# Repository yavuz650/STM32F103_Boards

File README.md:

# STM32F103 Boards
Rocket avionic boards, powered by the STM32F103C8T6 MCU.

This repository contains files and documentations of two avionic boards designed and developed for the Rocket Technologies Group of Istanbul Technical University in the year 2018. 

## Igniter Board
This board is designed to gather altitude data and control rocket's parachute deployment system. It was designed and programmed by Yavuz Selim Tozlu, assisted by Umit Yelken and L. Emre Top of Rocket Technologies Group.

## GPS Board
This board is designed to gather GPS data during flight, process it and send it to the ground station via the RF module attached to it. It was designed and programmed by Yavuz Selim Tozlu. 

Shout out goes to our [sponsor](http://www.megasistem.net) who was kind enough to manufacture the boards.

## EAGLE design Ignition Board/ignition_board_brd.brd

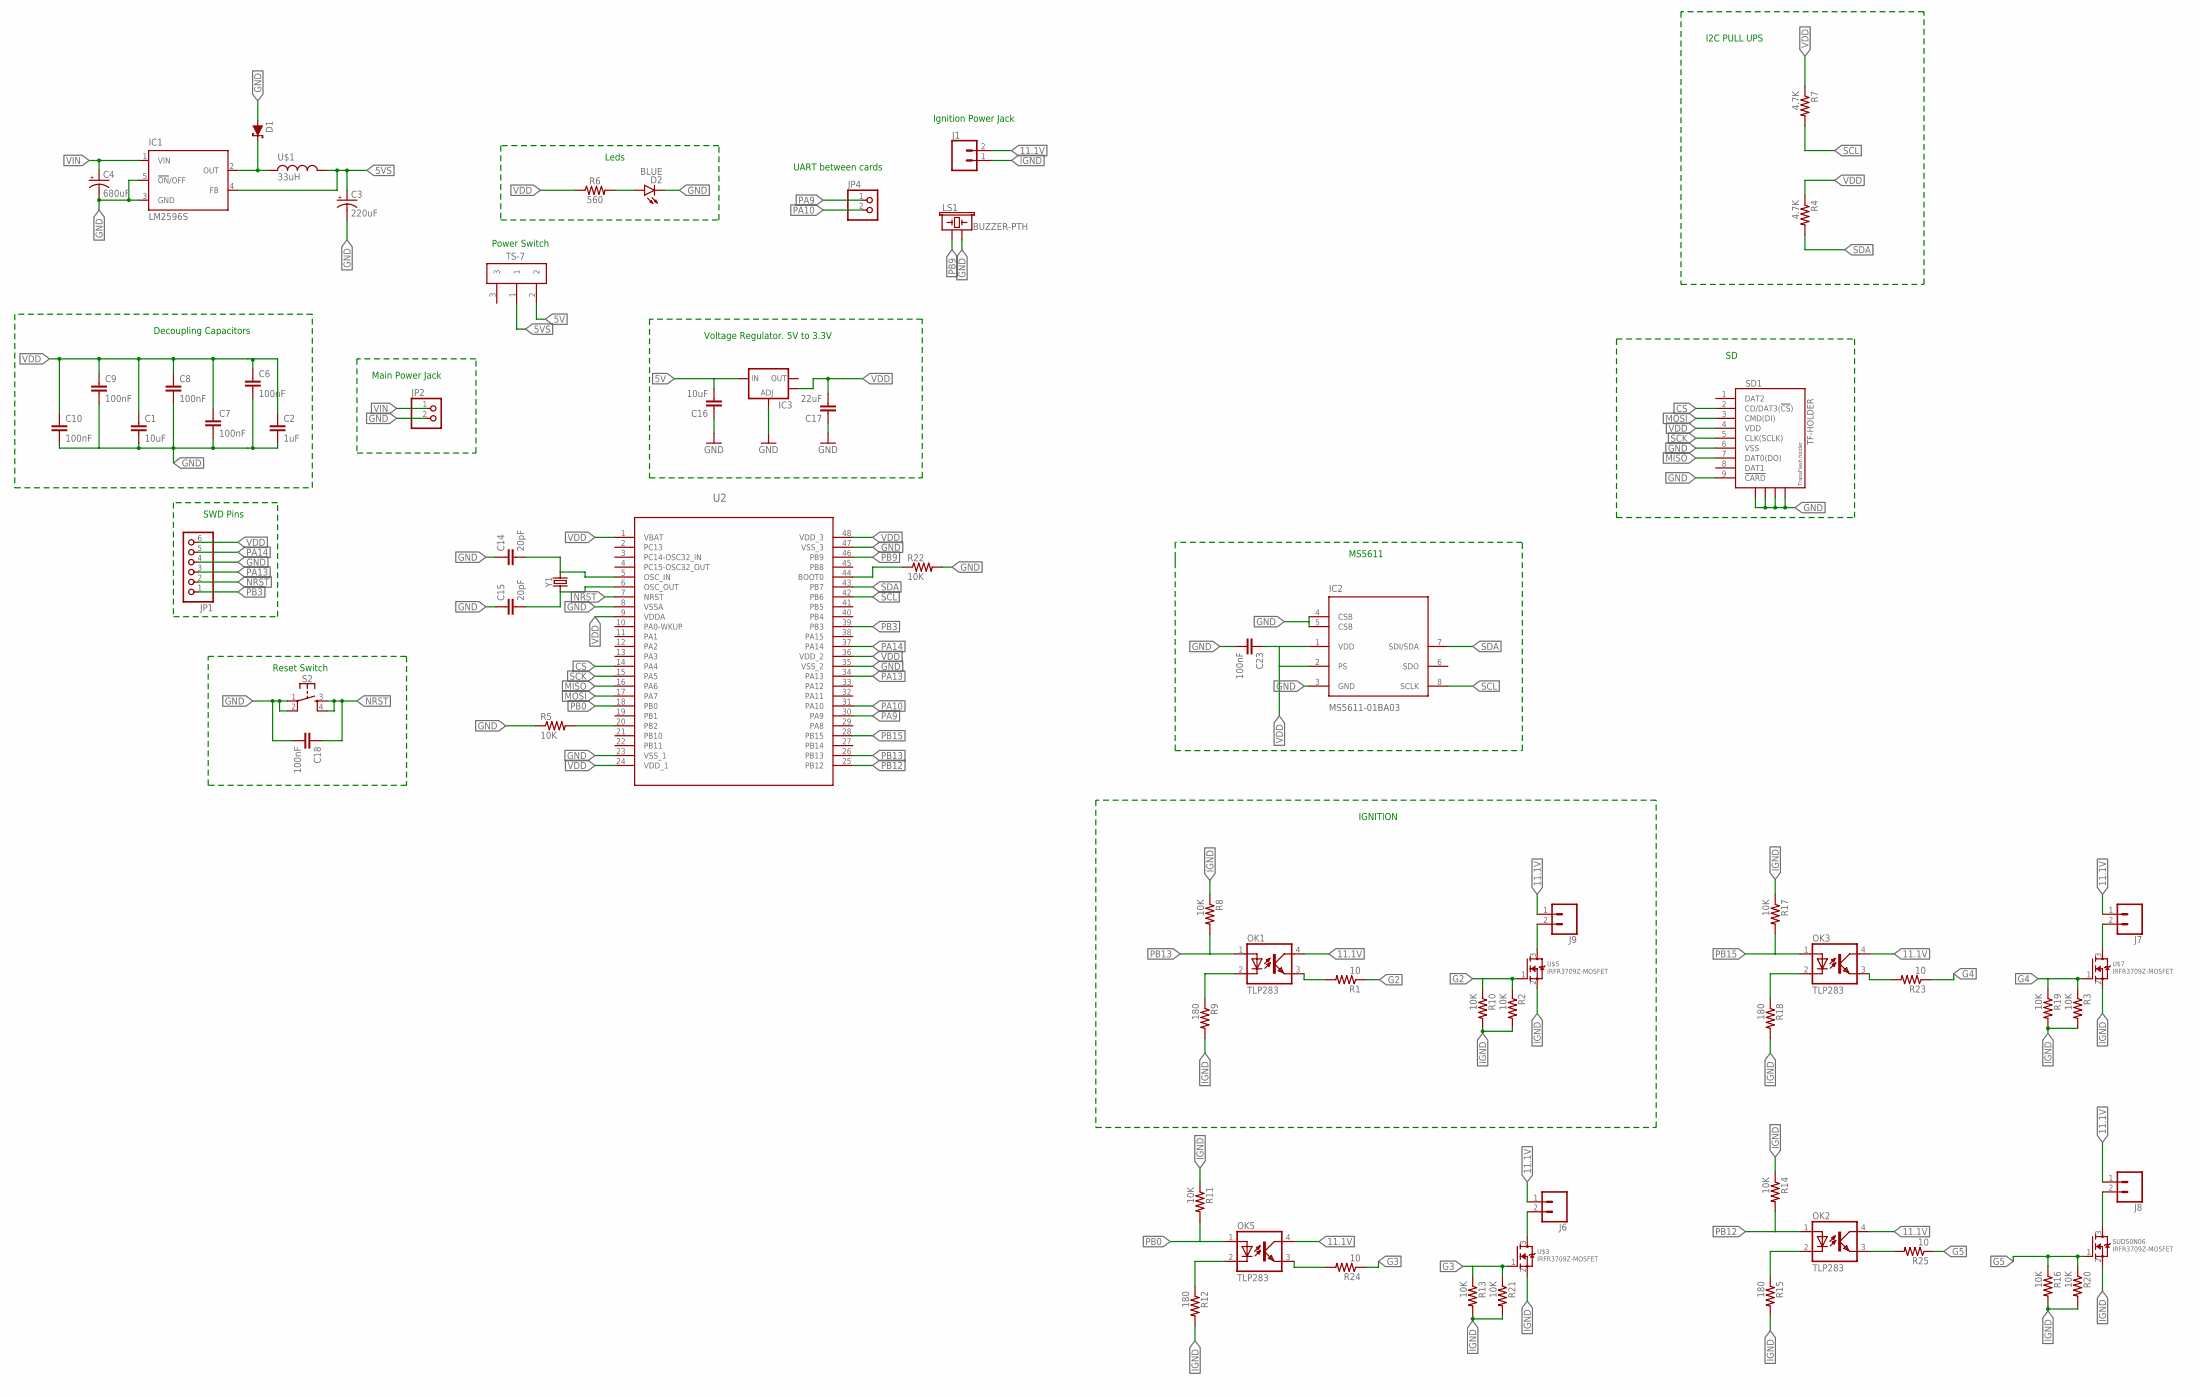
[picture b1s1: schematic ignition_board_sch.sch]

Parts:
C1: 10uF; 0805
C2: 1uF; 0805
C3: 220uF; TT5D7
C4: 680uF; TT5D7
C6, C7, C8, C9, C10, C18: 100nF; 0805
C14, C15: 20pF; 0805
C16: 10uF; 0805@2
C17: 22uF; 0805@2
C23: 100nF; 0805@2
D1: 3A/40V/500mV; SMA-DIODE
D2: BLUE; LED-1206
IC1: LM2596S; TO263-5
IC2: MS5611-01BA03; SON125P300X500X100-8N
IC3: V_REG_LM1117SOT223; SOT223
J1, J6, J7, J8, J9: CONN_025MM; SCREWTERMINAL-5MM-2
JP1: PINHD-1X6; 1X06
JP2: PINHD-1X2; 1X02
JP4: PINHD-1X2/90; 1X02/90
LS1: BUZZER-PTH; BUZZER-12MM
OK1, OK2, OK3, OK5: TLP283; MINI-FLAT-4
R1, R23, R24, R25: 10; 0805
R2, R3, R5, R8, R10, R11, R13, R14, R16, R17, R19, R20, R21, R22: 10K; 0805
R4, R7: 4.7K; 0805
R6: 560; 0805@1
R9, R12, R15, R18: 180; 0805
S2: MOMENTARY-SWITCH-SPST-2-SMD-5.2MM; TACTILE_SWITCH_SMD_5.2MM
SD1: TF-HOLDER; TF-PULL
SUD50N06: IRFR3709Z-MOSFET; TO252
TS-7: TS-7; TS7
U2: STM32F103CXT2; LQFP48-7X7MM
U$1: 33uH; MSS1260
U$3, U$5, U$7: IRFR3709Z-MOSFET; TO252
Y1: CRYSTALPTH-HC49US; HC49US

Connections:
5V: C16.2, IC3.3 (IN), TS-7.2
5VS: C3.+, IC1.4 (FB), TS-7.1, U$1.P$1
11.1V: J1.2, J6.1, J7.1, J8.1, J9.1, OK1.4 (COL), OK2.4 (COL), OK3.4 (COL), OK5.4 (COL)
CS: SD1.2 (CD/DAT3(!CS!)), U2.14 (PA4)
G2: R1.1, R2.1, R10.1, U$5.1 (G)
G3: R13.1, R21.1, R24.1, U$3.1 (G)
G4: R3.1, R19.1, R23.1, U$7.1 (G)
G5: R16.1, R20.1, R25.1, SUD50N06.1 (G)
GND: C1.2, C2.2, C3.-, C4.-, C6.2, C7.2, C8.2, C9.2, C10.2, C14.1, C15.1, C16.1, C17.1, C18.2, C23.2, D1.A, D2.C, IC1.3 (GND), IC1.5 (!ON!/OFF), IC2.3 (GND), IC2.4 (CSB), IC2.5 (CSB), IC3.1 (ADJ), JP1.4, JP2.2, LS1.- (2), R5.1, R22.2, S2.1, S2.2, SD1.6 (VSS), SD1.9 (!CARD), SD1.S1, SD1.S2, SD1.S3, SD1.S4, U2.8 (VSSA), U2.23 (VSS_1), U2.35 (VSS_2), U2.47 (VSS_3)
IGND: J1.1, R2.2, R3.2, R8.1, R9.2, R10.2, R11.1, R12.2, R13.2, R14.1, R15.2, R16.2, R17.1, R18.2, R19.2, R20.2, R21.2, SUD50N06.2 (S), U$3.2 (S), U$5.2 (S), U$7.2 (S)
MISO: SD1.7 (DAT0(DO)), U2.16 (PA6)
MOSI: SD1.3 (CMD(DI)), U2.17 (PA7)
unnamed: C15.2, U2.6 (OSC_OUT), Y1.1
unnamed: C14.2, U2.5 (OSC_IN), Y1.2
unnamed: R22.1, U2.44 (BOOT0)
unnamed: D1.C, IC1.2 (OUT), U$1.P$2
unnamed: OK1.3 (EMIT), R1.2
unnamed: R5.2, U2.20 (PB2)
unnamed: D2.A, R6.2
unnamed: OK2.3 (EMIT), R25.2
unnamed: J7.2, U$7.3 (D)
unnamed: J9.2, U$5.3 (D)
unnamed: J6.2, U$3.3 (D)
unnamed: OK3.3 (EMIT), R23.2
unnamed: OK5.2 (C), R12.1
unnamed: OK5.3 (EMIT), R24.2
unnamed: J8.2, SUD50N06.3 (D)
unnamed: OK2.2 (C), R15.1
unnamed: OK1.2 (C), R9.1
unnamed: OK3.2 (C), R18.1
NRST: C18.1, JP1.2, S2.3, S2.4, U2.7 (NRST)
PA9: JP4.1, U2.30 (PA9)
PA10: JP4.2, U2.31 (PA10)
PA13: JP1.3, U2.34 (PA13)
PA14: JP1.5, U2.37 (PA14)
PB0: OK5.1 (A), R11.2, U2.18 (PB0)
PB3: JP1.1, U2.39 (PB3)
PB9: LS1.+ (1), U2.46 (PB9)
PB12: OK2.1 (A), R14.2, U2.25 (PB12)
PB13: OK1.1 (A), R8.2, U2.26 (PB13)
PB15: OK3.1 (A), R17.2, U2.28 (PB15)
SCK: SD1.5 (CLK(SCLK)), U2.15 (PA5)
SCL: IC2.8 (SCLK), R7.2, U2.42 (PB6)
SDA: IC2.7 (SDI/SDA), R4.2, U2.43 (PB7)
VDD: C1.1, C2.1, C6.1, C7.1, C8.1, C9.1, C10.1, C17.2, C23.1, IC2.1 (VDD), IC2.2 (PS), IC3.4 (OUT), JP1.6, R4.1, R6.1, R7.1, SD1.4 (VDD), U2.1 (VBAT), U2.9 (VDDA), U2.24 (VDD_1), U2.36 (VDD_2), U2.48 (VDD_3)
VIN: C4.+, IC1.1 (VIN), JP2.1

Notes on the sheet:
Decoupling Capacitors
Voltage Regulator. 5V to 3.3V
Main Power Jack
Reset Switch
Leds
SWD Pins
MS5611
IGNITION
I2C PULL UPS
UART between cards
Power Switch
Ignition Power Jack

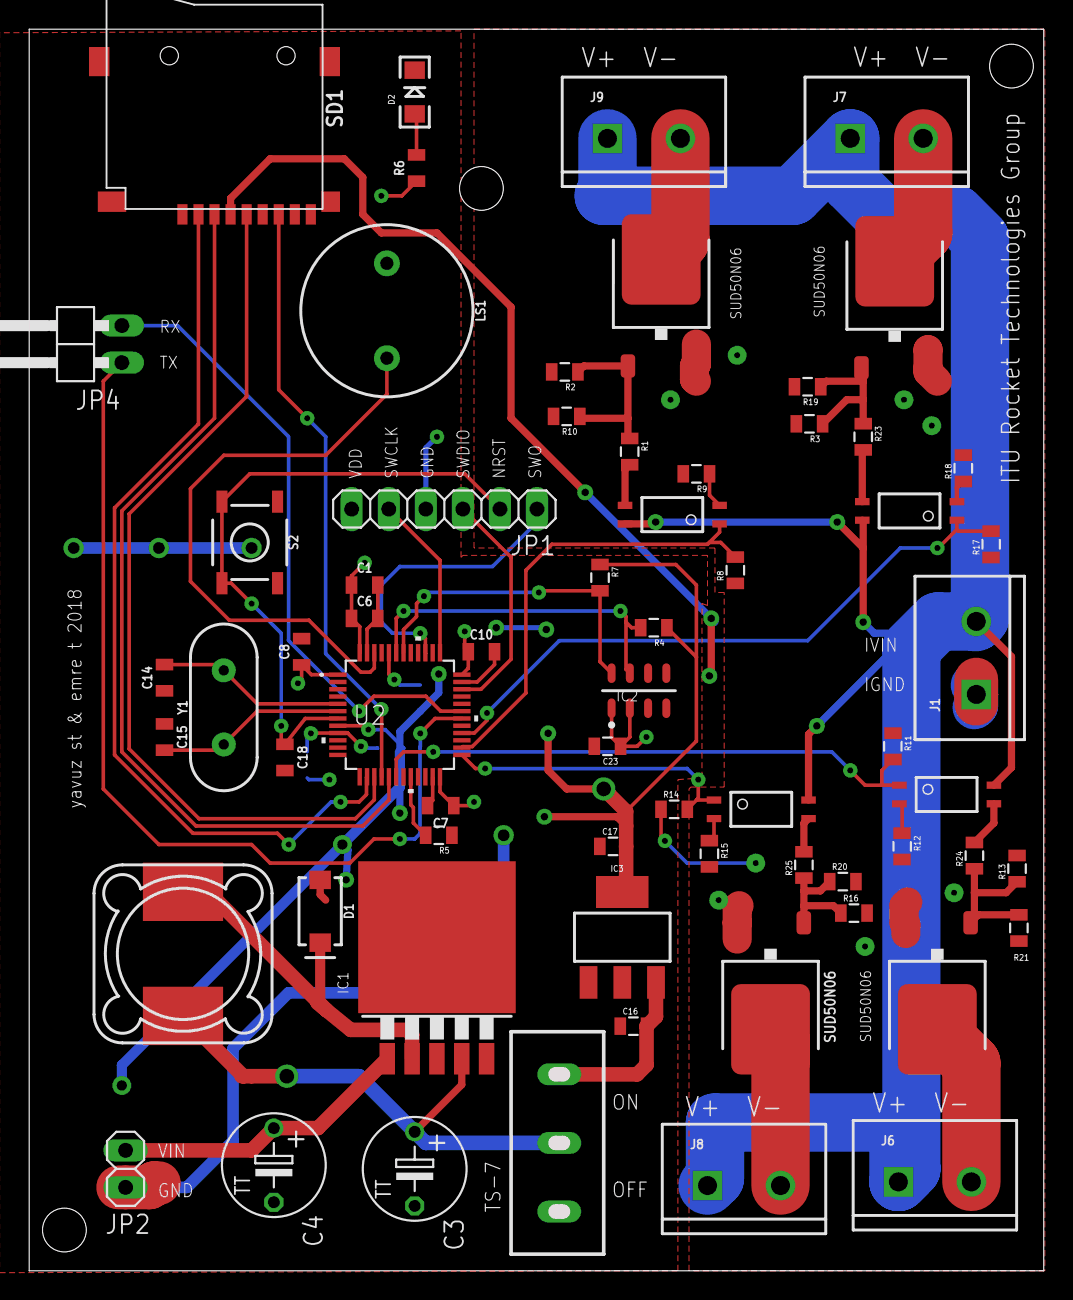
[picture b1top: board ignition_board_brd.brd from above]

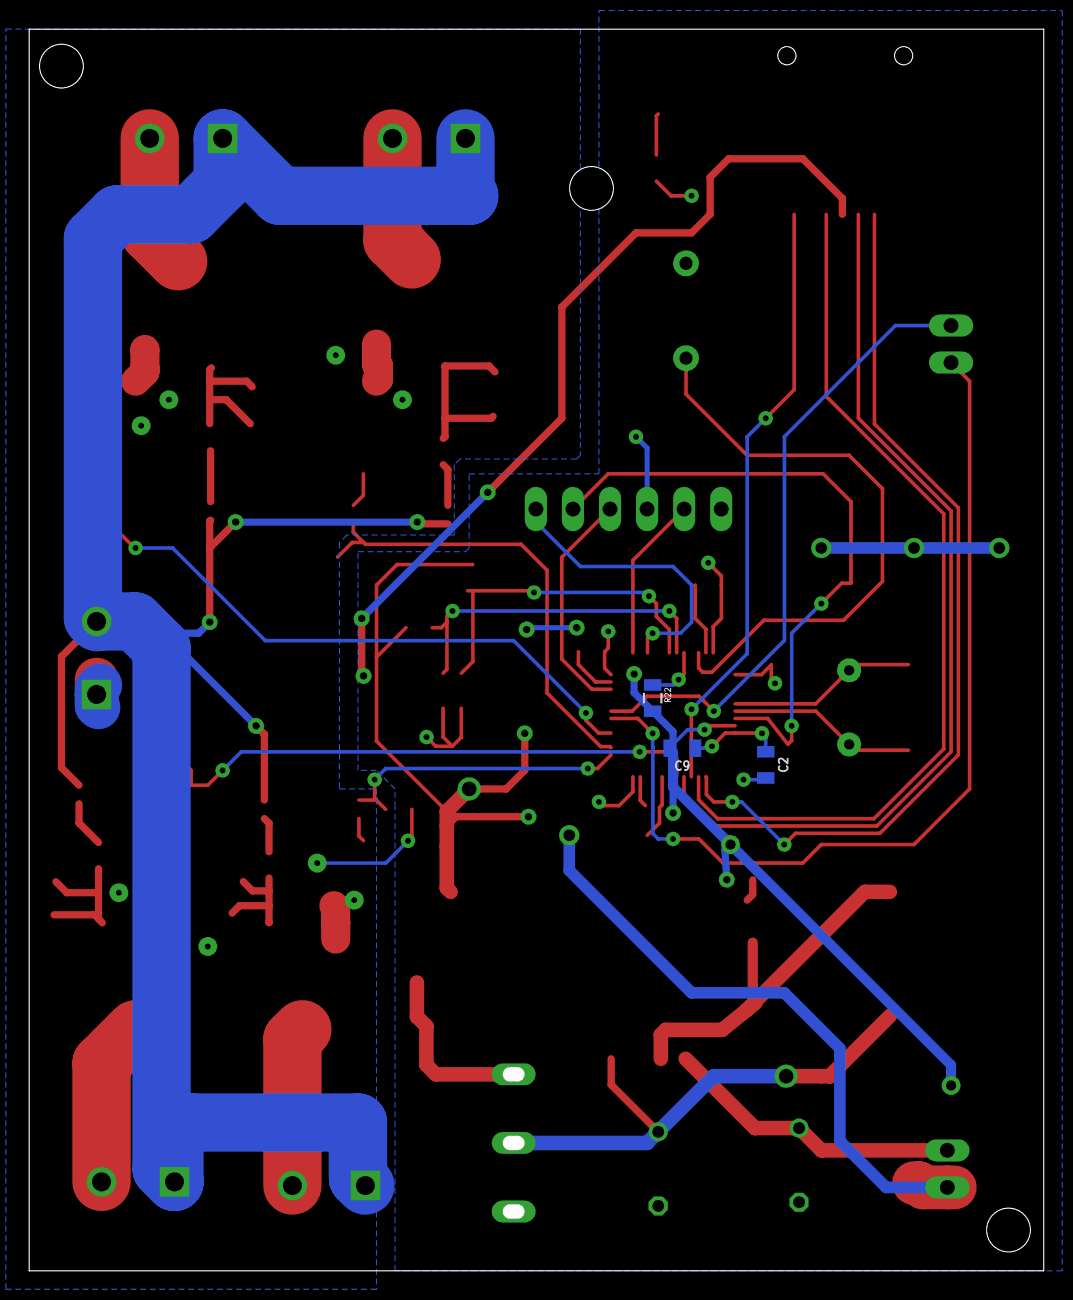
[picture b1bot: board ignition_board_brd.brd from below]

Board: 2 copper layers, 68.5 x 84.1 mm, 68 parts (3 on the bottom side), 46 nets.

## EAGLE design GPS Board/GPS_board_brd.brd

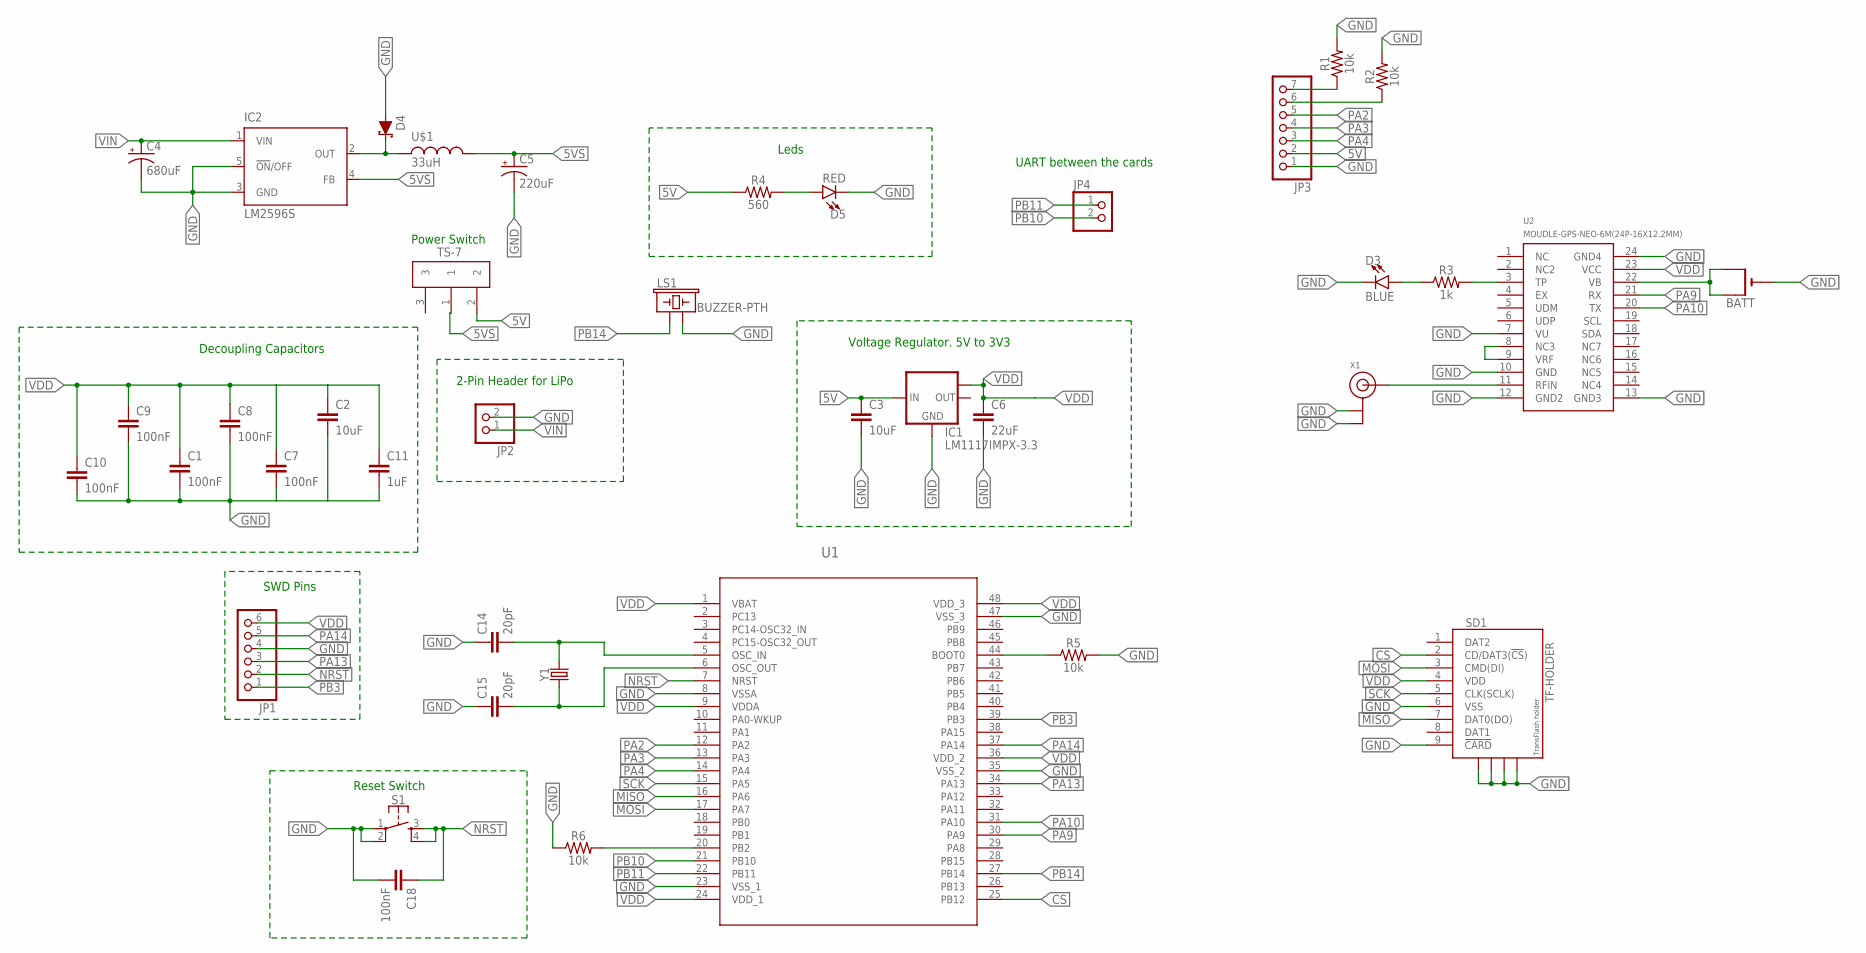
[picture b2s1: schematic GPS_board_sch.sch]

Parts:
BATT: CR1220SMT; CR1220-SMD
C1, C7, C8, C9, C10, C18: 100nF; 0805
C2, C3: 10uF; 0805
C4: 680uF; TT5D7
C5: 220uF; TT5D7
C6: 22uF; 0805
C11: 1uF; 0805
C14, C15: 20pF; 0805
D3: BLUE; LED-1206
D4: 3A/40V/500mV; SMA-DIODE
D5: RED; LED-1206
IC1: LM1117IMPX-3.3; SOT223
IC2: LM2596S; TO263-5
JP1: PINHD-1X6; 1X06
JP2: PINHD-1X2; 1X02
JP3: PINHD-1X7; 1X07
JP4: PINHD-1X2/90; 1X02/90
LS1: BUZZER-PTH; BUZZER-12MM
R1, R2, R5, R6: 10k; 0805
R3: 1k; 0805
R4: 560; 0805
S1: MOMENTARY-SWITCH-SPST-2-SMD-5.2MM; TACTILE_SWITCH_SMD_5.2MM
SD1: TF-HOLDER; TF-PULL
TS-7: TS-7; TS7
U1: STM32F103CXT2; LQFP48-7X7MM
U2: MOUDLE-GPS-NEO-6M(24P-16X12.2MM); GPS24P-SMD-1.1-16X12.2MM
U$1: 33uH; MSS1260
X1: ANTENNA_U.FL; U.FL
Y1: CRYSTALPTH-HC49US; HC49US

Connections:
5V: C3.1, IC1.3 (IN), JP3.2, R4.1, TS-7.2
5VS: C5.+, IC2.4 (FB), TS-7.1, U$1.P$1
CS: SD1.2 (CD/DAT3(!CS!)), U1.25 (PB12)
GND: BATT.-, C1.2, C2.2, C3.2, C4.-, C5.-, C6.2, C7.2, C8.2, C9.2, C10.2, C11.2, C14.1, C15.1, C18.2, D3.C, D4.A, D5.C, IC1.1 (GND), IC2.3 (GND), IC2.5 (!ON!/OFF), JP1.4, JP2.2, JP3.1, LS1.- (2), R1.2, R2.2, R5.2, R6.1, S1.1, S1.2, SD1.6 (VSS), SD1.9 (!CARD), SD1.S1, SD1.S2, SD1.S3, SD1.S4, U1.8 (VSSA), U1.23 (VSS_1), U1.35 (VSS_2), U1.47 (VSS_3), U2.7 (VU), U2.10 (GND), U2.12 (GND2), U2.13 (GND3), U2.24 (GND4), X1.1 (GND), X1.2 (GND)
MISO: SD1.7 (DAT0(DO)), U1.16 (PA6)
MOSI: SD1.3 (CMD(DI)), U1.17 (PA7)
unnamed: C14.2, U1.5 (OSC_IN), Y1.2
unnamed: C15.2, U1.6 (OSC_OUT), Y1.1
unnamed: BATT.+$1 (+), BATT.+$2 (+1), U2.22 (VB)
unnamed: U2.11 (RFIN), X1.3 (SIGNAL)
unnamed: R5.1, U1.44 (BOOT0)
unnamed: R6.2, U1.20 (PB2)
unnamed: D4.C, IC2.2 (OUT), U$1.P$2
unnamed: D5.A, R4.2
unnamed: U2.8 (NC3), U2.9 (VRF)
unnamed: R3.2, U2.3 (TP)
unnamed: D3.A, R3.1
unnamed: JP3.7, R1.1
unnamed: JP3.6, R2.1
NRST: C18.1, JP1.2, S1.3, S1.4, U1.7 (NRST)
PA2: JP3.5, U1.12 (PA2)
PA3: JP3.4, U1.13 (PA3)
PA4: JP3.3, U1.14 (PA4)
PA9: U1.30 (PA9), U2.21 (RX)
PA10: U1.31 (PA10), U2.20 (TX)
PA13: JP1.3, U1.34 (PA13)
PA14: JP1.5, U1.37 (PA14)
PB3: JP1.1, U1.39 (PB3)
PB10: JP4.2, U1.21 (PB10)
PB11: JP4.1, U1.22 (PB11)
PB14: LS1.+ (1), U1.27 (PB14)
SCK: SD1.5 (CLK(SCLK)), U1.15 (PA5)
VDD: C1.1, C2.1, C6.1, C7.1, C8.1, C9.1, C10.1, C11.1, IC1.TAB (OUT1), JP1.6, SD1.4 (VDD), U1.1 (VBAT), U1.9 (VDDA), U1.24 (VDD_1), U1.36 (VDD_2), U1.48 (VDD_3), U2.23 (VCC)
VIN: C4.+, IC2.1 (VIN), JP2.1

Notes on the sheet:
Decoupling Capacitors
Voltage Regulator. 5V to 3V3
2-Pin Header for LiPo
Reset Switch
Leds
SWD Pins
UART between the cards
Power Switch

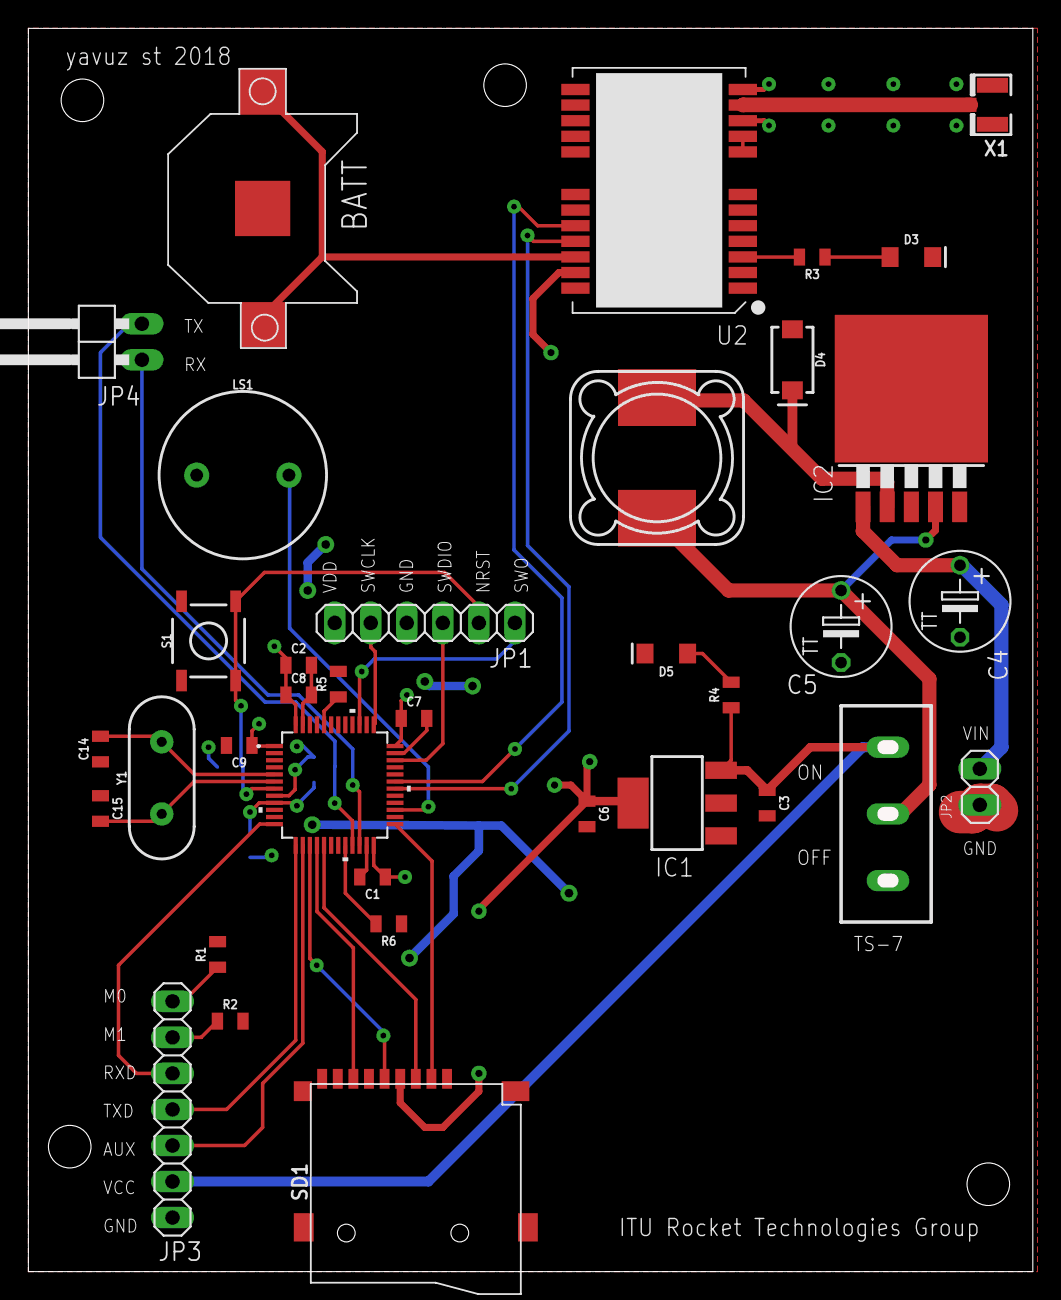
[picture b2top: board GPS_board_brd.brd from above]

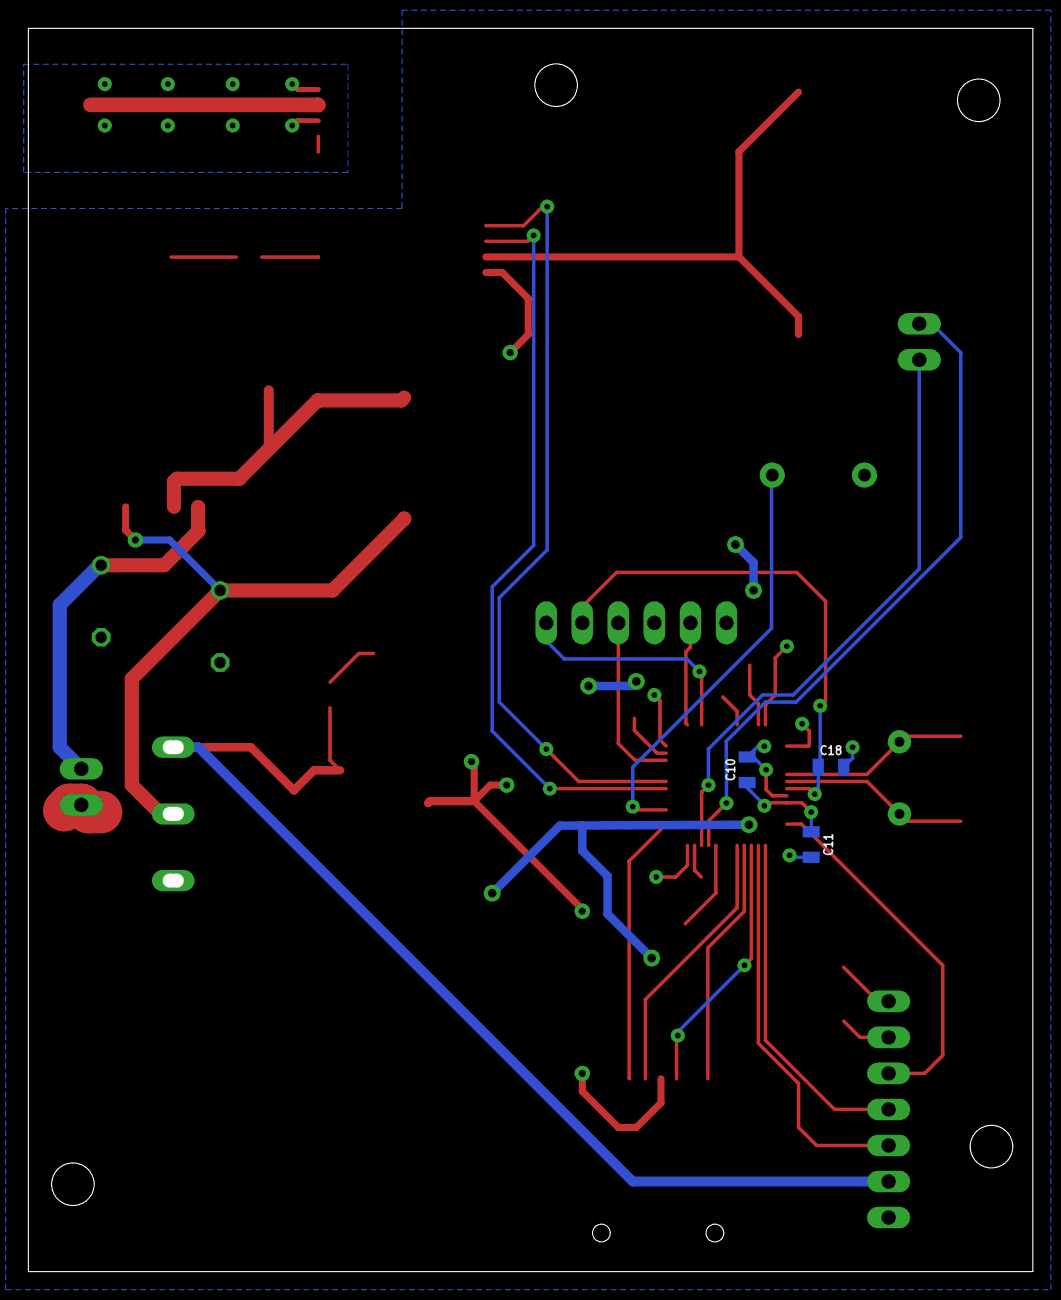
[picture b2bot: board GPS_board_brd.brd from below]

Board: 2 copper layers, 69.8 x 86.6 mm, 39 parts (3 on the bottom side), 34 nets.

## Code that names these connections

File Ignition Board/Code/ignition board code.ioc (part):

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Mcu.Name=STM32F103C(8-B)Tx
Mcu.Package=LQFP48
Mcu.UserName=STM32F103C8Tx
PA10.Mode=Asynchronous
PA10.Signal=USART1_RX
PA13.Mode=Serial_Wire
PA13.Signal=SYS_JTMS-SWDIO
PA14.Mode=Serial_Wire
PA14.Signal=SYS_JTCK-SWCLK
PA4.Signal=GPIO_Output
PA5.Mode=Full_Duplex_Master
PA5.Signal=SPI1_SCK
PA6.Mode=Full_Duplex_Master
PA6.Signal=SPI1_MISO
PA7.Mode=Full_Duplex_Master
PA7.Signal=SPI1_MOSI
PA9.Mode=Asynchronous
PA9.Signal=USART1_TX
PB0.Signal=GPIO_Output
PB12.Signal=GPIO_Output
PB13.Signal=GPIO_Output
PB15.Signal=GPIO_Output
PB6.Mode=I2C
PB6.Signal=I2C1_SCL
PB7.Mode=I2C
PB7.Signal=I2C1_SDA
PB9.Signal=GPIO_Output
PD0-OSC_IN.Mode=HSE-External-Oscillator
PD0-OSC_IN.Signal=RCC_OSC_IN
PD1-OSC_OUT.Mode=HSE-External-Oscillator
PD1-OSC_OUT.Signal=RCC_OSC_OUT
RCC.SYSCLKFreq_VALUE=72000000
RCC.SYSCLKSource=RCC_SYSCLKSOURCE_PLLCLK
board=ignition board code

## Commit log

2018-09-05 dummy file
2018-09-05 added board files
2018-09-05 Create dummy
2018-09-17 uploaded the report
    initial release
2018-09-21 Added Keil uVision 5 project folder. Generated by the CubeMX
2018-09-23 removed old files

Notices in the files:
parts and their libraries:
SparkFun-Capacitors: Licensing: Creative Commons ShareAlike 4.0 International - https://creativecommons.org/licenses/by-sa/4.0
